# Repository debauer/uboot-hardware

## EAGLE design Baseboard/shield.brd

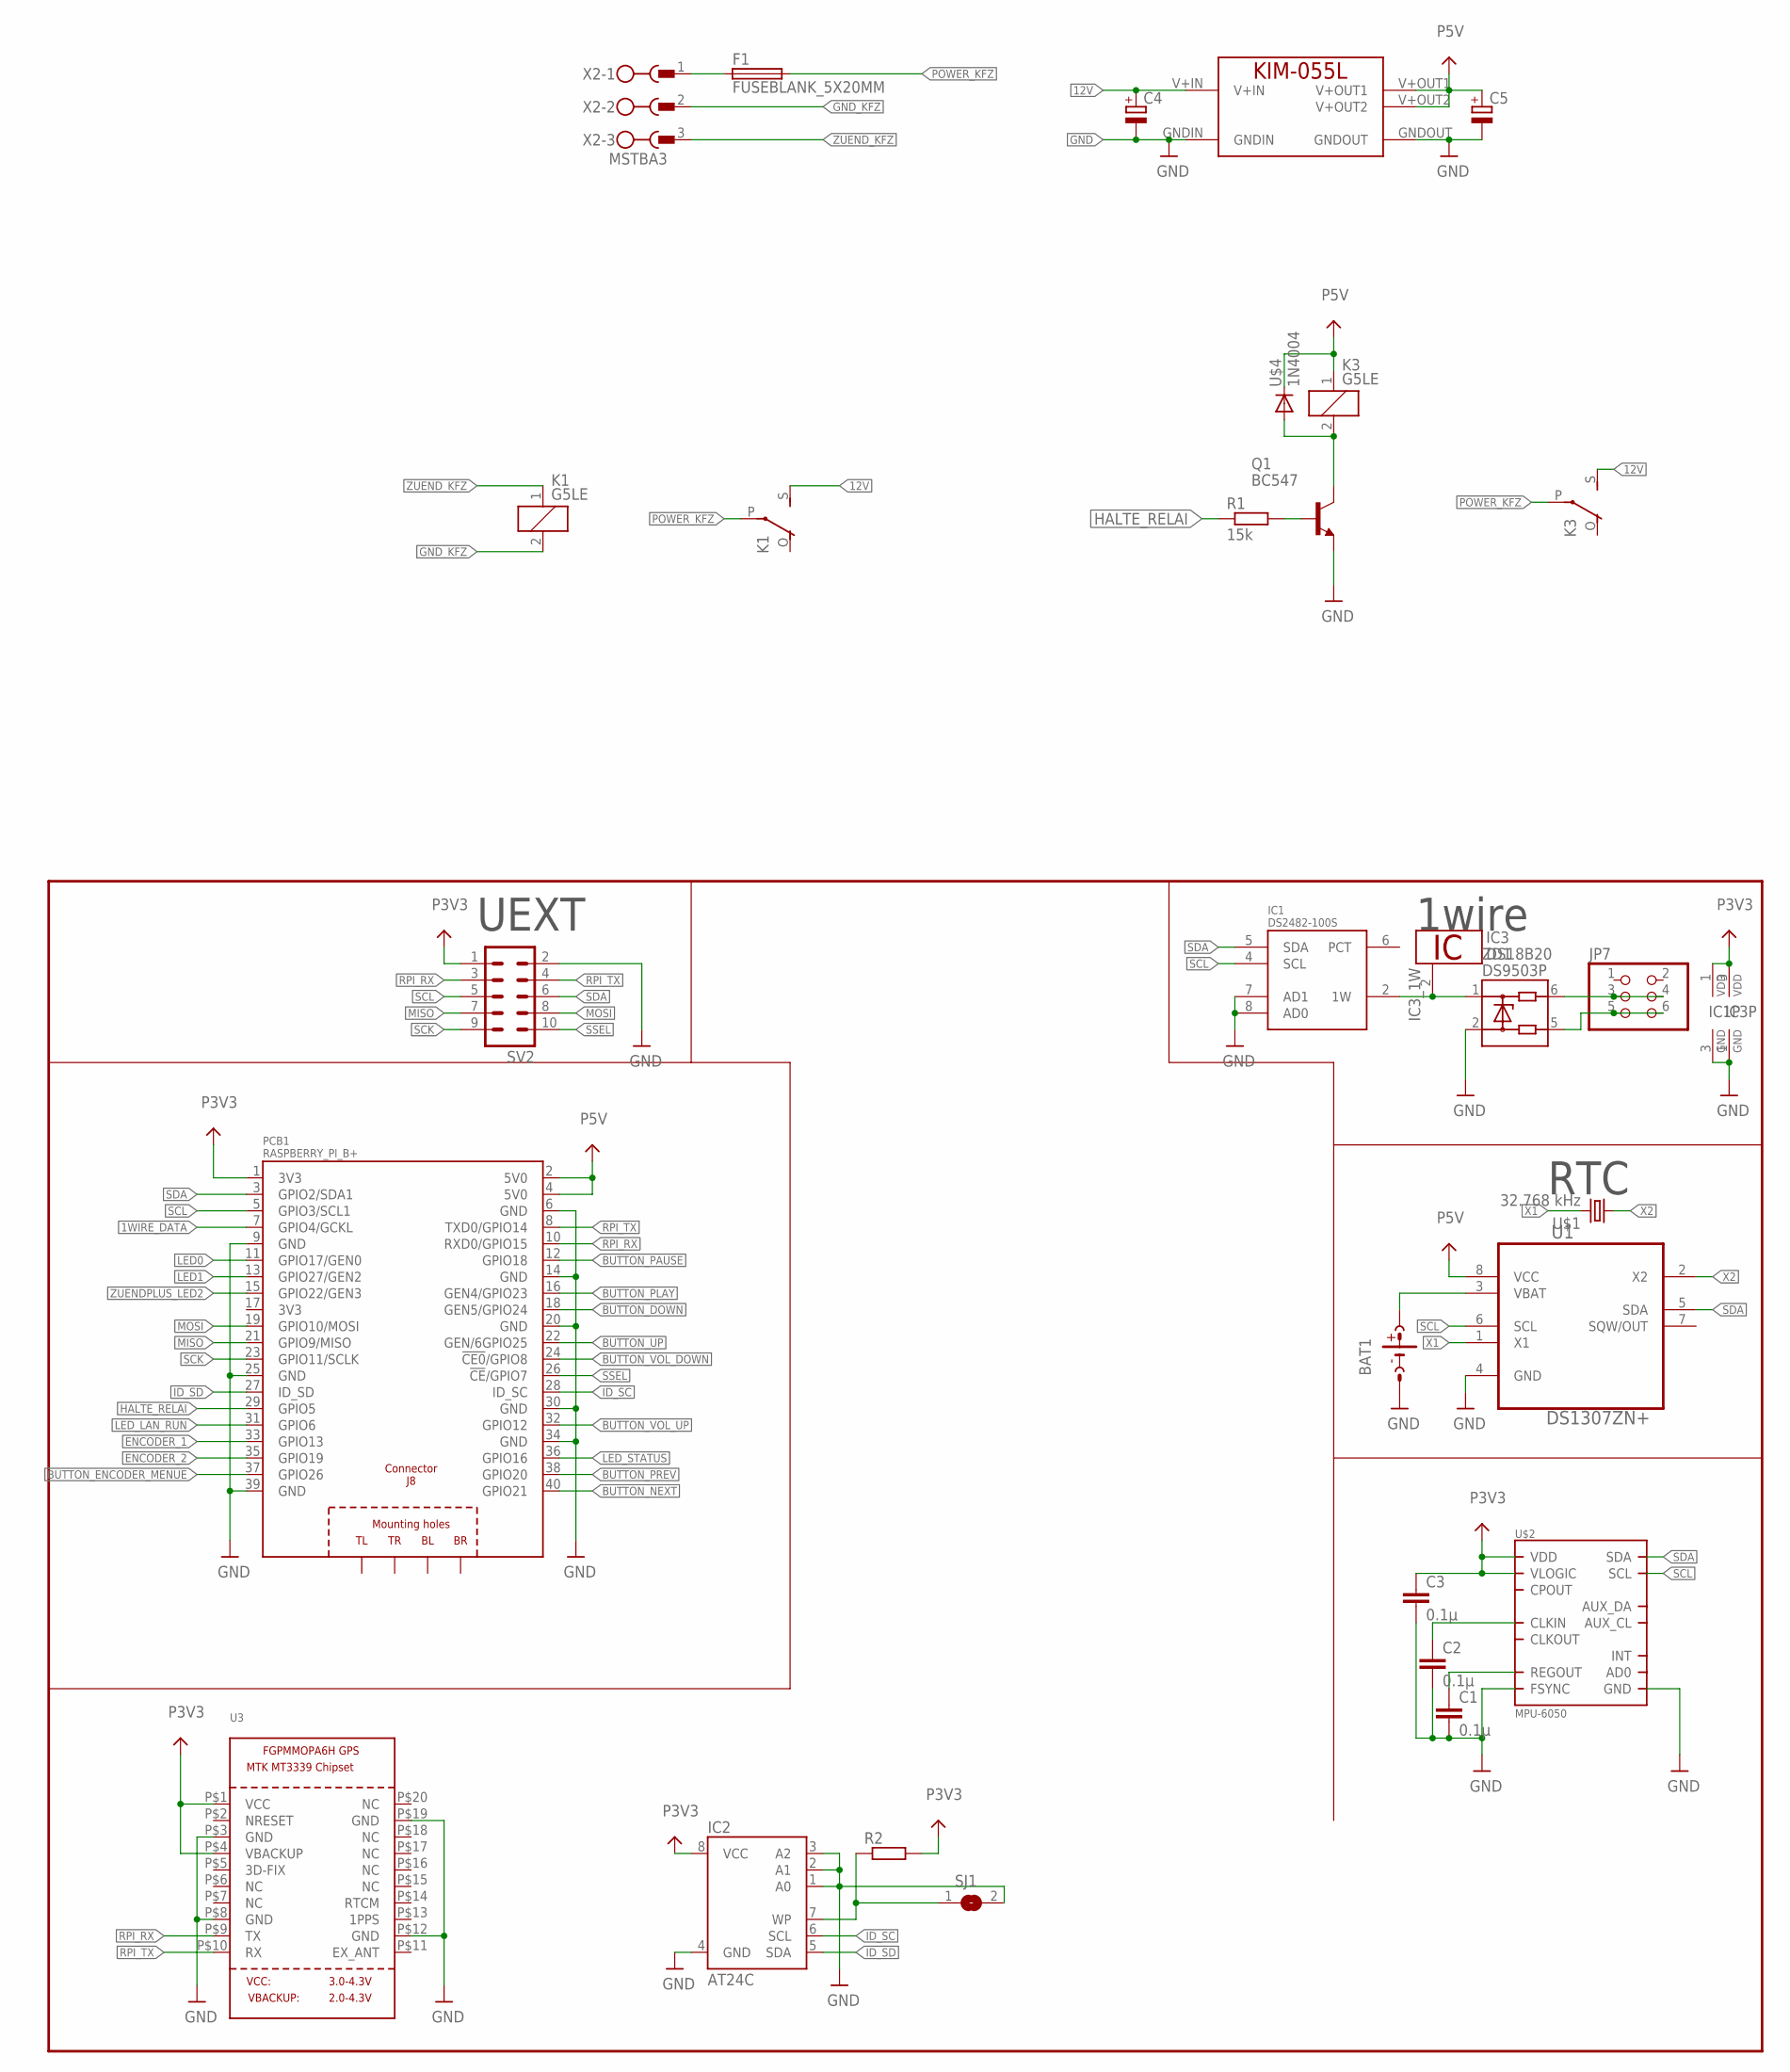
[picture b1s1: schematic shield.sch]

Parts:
BAT1: CR2032; CR2032-SOCKET
C1, C2, C3: 0.1µ; C0805
C4, C5: CPOL-EUE5-13; E5-13
F1: FUSEBLANK_5X20MM; FUSE_HOLDER_5X20MM
IC1: DS2482-100S; SO08
IC2: AT24C; SO08
IC3: DS18B20; TO92-
JP7: PINHD-2X3/90; 2X03/90
K1, K3: G5LE
MOD1: KIM-055L
PCB1: RASPBERRY_PI_B+
Q1: BC547; TO92
R1: 15k; 0207/7
R2: R-EU_R0805; R0805
SJ1: SJM
SV2: ML10
U1: DS1307ZN+; SOIC127P600X175-8N
U3: GPS_FGPMMOPA6H; FGPMMOPA6H
U$1: 32.768 kHz; CC5
U$2: MPU-6050; QFN.24.4X4
U$4: 1N4004; DO41-10
X2: MSTBA3
ZD1: DS9503P; TSOC6

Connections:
1WIRE_DATA: IC1.2 (1W), IC3.2 (1W), PCB1.7 (GPIO4/GCKL), ZD1.1
12V: C4.+, K1.S, K3.S, MOD1.V+IN
BUTTON_DOWN: PCB1.18 (GEN5/GPIO24)
BUTTON_ENCODER_MENUE: PCB1.37 (GPIO26)
BUTTON_NEXT: PCB1.40 (GPIO21)
BUTTON_PAUSE: PCB1.12 (GPIO18)
BUTTON_PLAY: PCB1.16 (GEN4/GPIO23)
BUTTON_PREV: PCB1.38 (GPIO20)
BUTTON_UP: PCB1.22 (GEN/6GPIO25)
BUTTON_VOL_DOWN: PCB1.24 (!CE0!/GPIO8)
BUTTON_VOL_UP: PCB1.32 (GPIO12)
ENCODER_1: PCB1.33 (GPIO13)
ENCODER_2: PCB1.35 (GPIO19)
GND: BAT1.M (NEG), C1.2, C2.2, C3.2, C4.-, C5.-, IC1.3 (GND), IC1.7 (AD1), IC1.8 (AD0), IC2.1 (A0), IC2.2 (A1), IC2.3 (A2), IC2.4 (GND), IC3.1 (GND), MOD1.GNDIN, MOD1.GNDOUT, PCB1.6 (GND), PCB1.14 (GND), PCB1.20 (GND), PCB1.30 (GND), PCB1.34 (GND), Q1.1 (E), SJ1.2, SV2.2, U1.4 (GND), U3.P$3 (GND), U3.P$8 (GND), U3.P$12 (GND), U3.P$19 (GND), U$2.11 (FSYNC), U$2.18 (GND), ZD1.2
GND@1: PCB1.9 (GND), PCB1.25 (GND), PCB1.39 (GND)
GND_KFZ: K1.2, X2.2
HALTE_RELAI: PCB1.29 (GPIO5), R1.1
ID_SC: IC2.6 (SCL), PCB1.28 (ID_SC)
ID_SD: IC2.5 (SDA), PCB1.27 (ID_SD)
LED0: PCB1.11 (GPIO17/GEN0)
LED1: PCB1.13 (GPIO27/GEN2)
LED_LAN_RUN: PCB1.31 (GPIO6)
LED_STATUS: PCB1.36 (GPIO16)
MISO: PCB1.21 (GPIO9/MISO), SV2.7
MOSI: PCB1.19 (GPIO10/MOSI), SV2.8
unnamed: BAT1.P (POS2), U1.3 (VBAT)
unnamed: K3.2, Q1.3 (C), U$4.A
unnamed: C1.1, U$2.10 (REGOUT)
unnamed: C2.1, U$2.1 (CLKIN)
unnamed: IC2.7 (WP), R2.1, SJ1.1
unnamed: Q1.2 (B), R1.2
unnamed: F1.1, X2.1
unnamed: JP7.3, JP7.4, ZD1.6
unnamed: JP7.5, JP7.6, ZD1.5
P3V3: C3.1, IC1.1 (VDD), IC2.8 (VCC), IC3.3 (VDD), PCB1.1 (3V3), R2.2, SV2.1, U3.P$1 (VCC), U3.P$4 (VBACKUP), U$2.8 (VLOGIC), U$2.13 (VDD)
P5V: C5.+, K3.1, MOD1.V+OUT1, MOD1.V+OUT2, PCB1.2 (5V0), PCB1.4 (5V0), U1.8 (VCC), U$4.C
POWER_KFZ: F1.2, K1.P, K3.P
RPI_RX: PCB1.10 (RXD0/GPIO15), SV2.3, U3.P$9 (TX)
RPI_TX: PCB1.8 (TXD0/GPIO14), SV2.4, U3.P$10 (RX)
SCK: PCB1.23 (GPIO11/SCLK), SV2.9
SCL: IC1.4 (SCL), PCB1.5 (GPIO3/SCL1), SV2.5, U1.6 (SCL), U$2.23 (SCL)
SDA: IC1.5 (SDA), PCB1.3 (GPIO2/SDA1), SV2.6, U1.5 (SDA), U$2.24 (SDA)
SSEL: PCB1.26 (!CE!/GPIO7), SV2.10
X1: U1.1 (X1), U$1.P$2 (2)
X2: U1.2 (X2), U$1.P$1 (1)
ZUENDPLUS_LED2: PCB1.15 (GPIO22/GEN3)
ZUEND_KFZ: K1.1, X2.3

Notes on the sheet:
1wire
RTC
UEXT

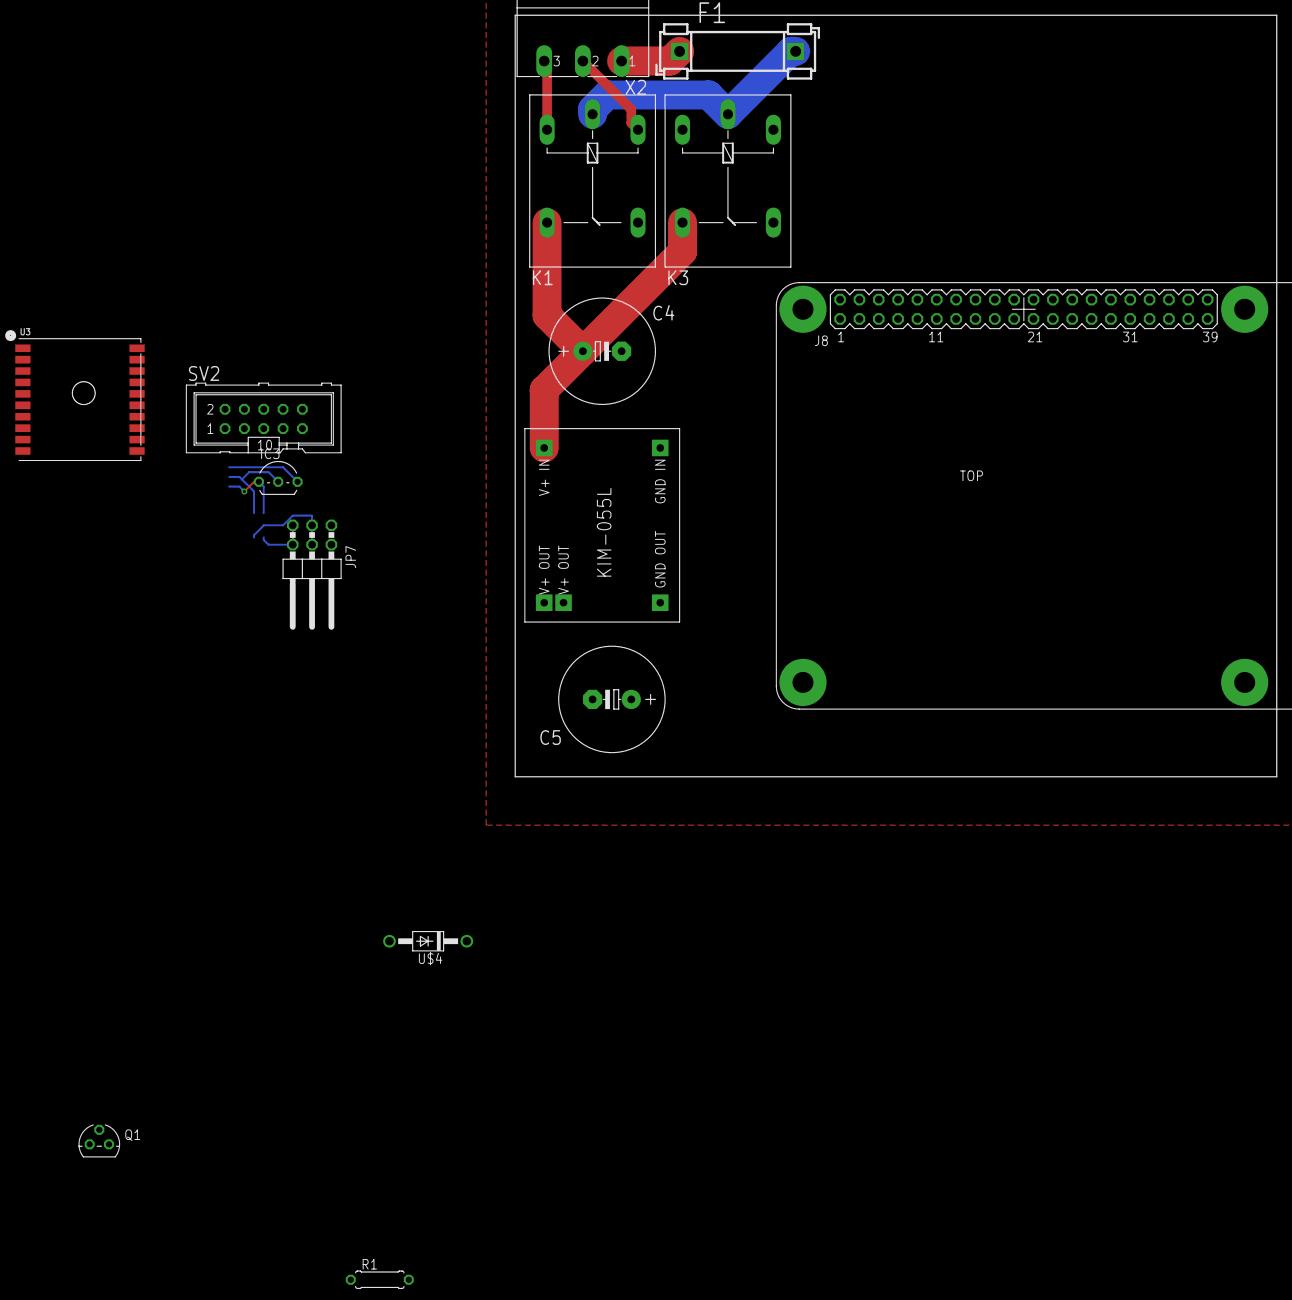
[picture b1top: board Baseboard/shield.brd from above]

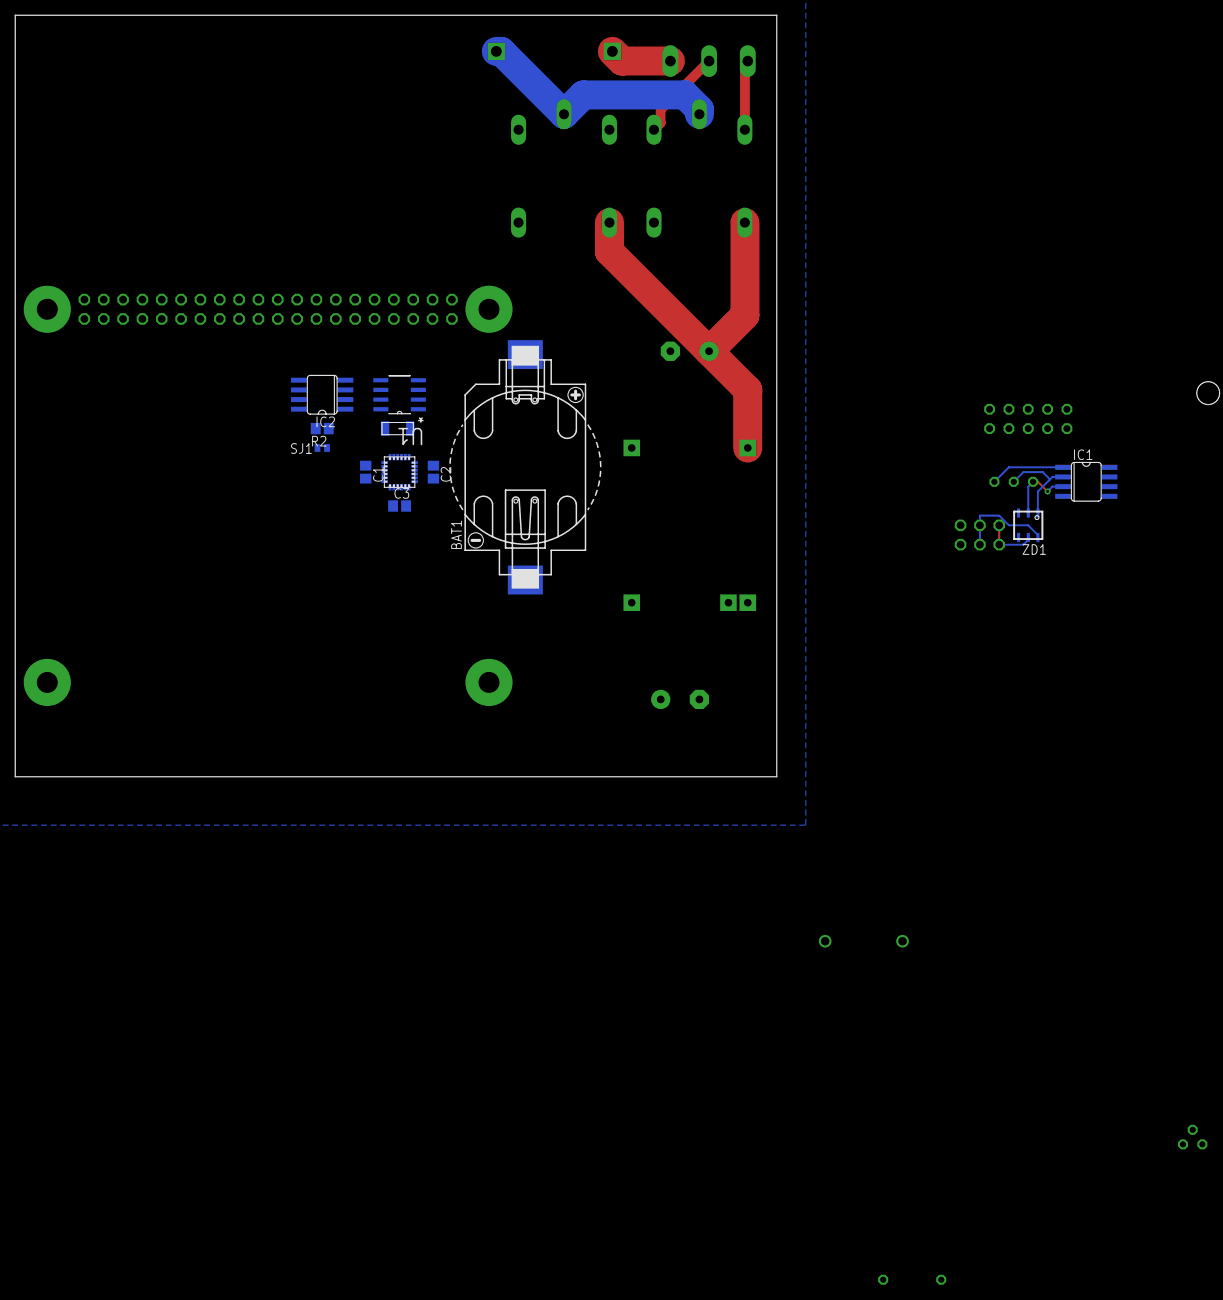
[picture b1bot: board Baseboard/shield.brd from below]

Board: 2 copper layers, 100.0 x 100.0 mm, 27 parts (12 on the bottom side), 31 nets.

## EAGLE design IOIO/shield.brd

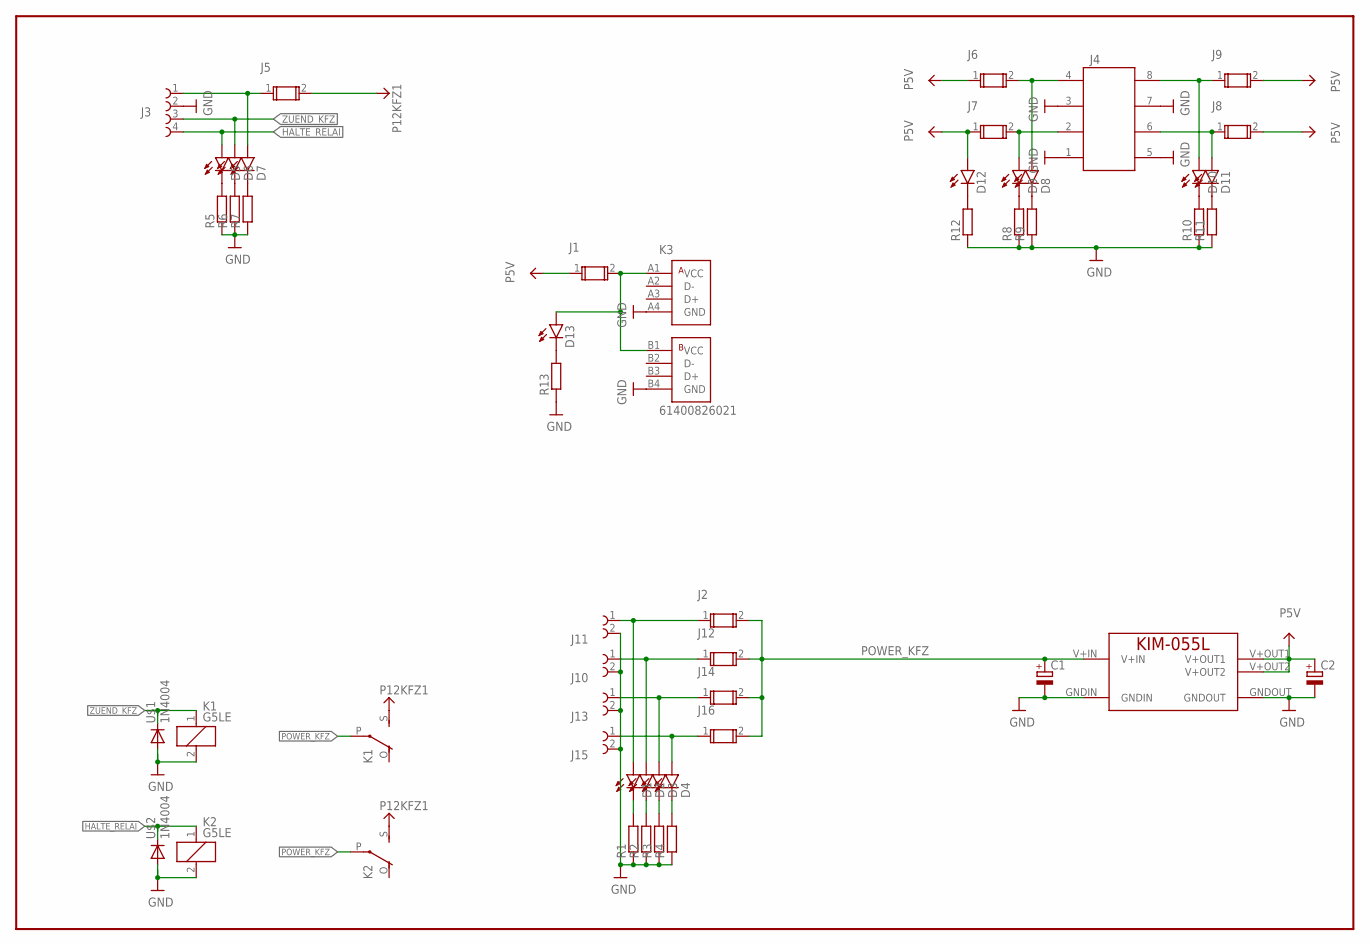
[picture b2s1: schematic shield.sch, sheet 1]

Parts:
C1, C2: CPOL-EUE5-13; E5-13
D1, D2, D3, D4, D5, D6, D7, D8, D9, D10, D11, D12, D13: LED-3MM-NO_SILK; LED3MM-NS
J1, J2, J5, J6, J7, J8, J9, J12, J14, J16: 696101000002
J3: 691325110004
J4: 691327310008
J10, J11, J13, J15: 691322110002
K1, K2: G5LE
K3: 61400826021
MOD1: KIM-055L
R1, R2, R3, R4, R5, R6, R7, R8, R9, R10, R11, R12, R13: R-EU_0309/V; 0309V
U$1, U$2: 1N4004; DO41-10

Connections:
GND: C1.-, C2.-, J3.2 (3), J4.1, J4.3 (5), J4.5 (2), J4.7 (6), J10.2 (1), J11.2 (1), J13.2 (1), J15.2 (1), K1.2, K2.2, K3.A4 (GND), K3.B4 (GND), MOD1.GNDIN, MOD1.GNDOUT, R1.1, R2.1, R3.1, R4.1, R5.1, R6.1, R7.1, R8.1, R9.1, R10.1, R11.1, R12.1, R13.1, U$1.A, U$2.A
HALTE_RELAI: D5.A, J3.4 (1), K2.1, U$2.C
unnamed: D7.A, J3.1 (4), J5.1
unnamed: D11.A, J4.6 (4), J8.1
unnamed: D1.A, J2.1, J11.1 (2)
unnamed: D10.A, J4.8, J9.1
unnamed: D8.A, J4.4 (7), J6.2
unnamed: D9.A, J4.2 (3), J7.2
unnamed: D2.A, J10.1 (2), J12.1
unnamed: D3.A, J13.1 (2), J14.1
unnamed: D4.A, J15.1 (2), J16.1
unnamed: D1.K (C), R1.2
unnamed: D2.K (C), R2.2
unnamed: D3.K (C), R3.2
unnamed: D4.K (C), R4.2
unnamed: D5.K (C), R5.2
unnamed: D6.K (C), R6.2
unnamed: D7.K (C), R7.2
unnamed: D12.K (C), R12.2
unnamed: D9.K (C), R8.2
unnamed: D8.K (C), R9.2
unnamed: D10.K (C), R10.2
unnamed: D11.K (C), R11.2
unnamed: D13.A, J1.2, K3.A1 (VCC), K3.B1 (VCC)
unnamed: D13.K (C), R13.2
P5V: C2.+, D12.A, J1.1, J6.1, J7.1, J8.2, J9.2, MOD1.V+OUT1, MOD1.V+OUT2
P12KFZ1: J5.2, K1.S, K2.S
POWER_KFZ: C1.+, J2.2, J12.2, J14.2, J16.2, K1.P, K2.P, MOD1.V+IN
ZUEND_KFZ: D6.A, J3.3 (2), K1.1, U$1.C

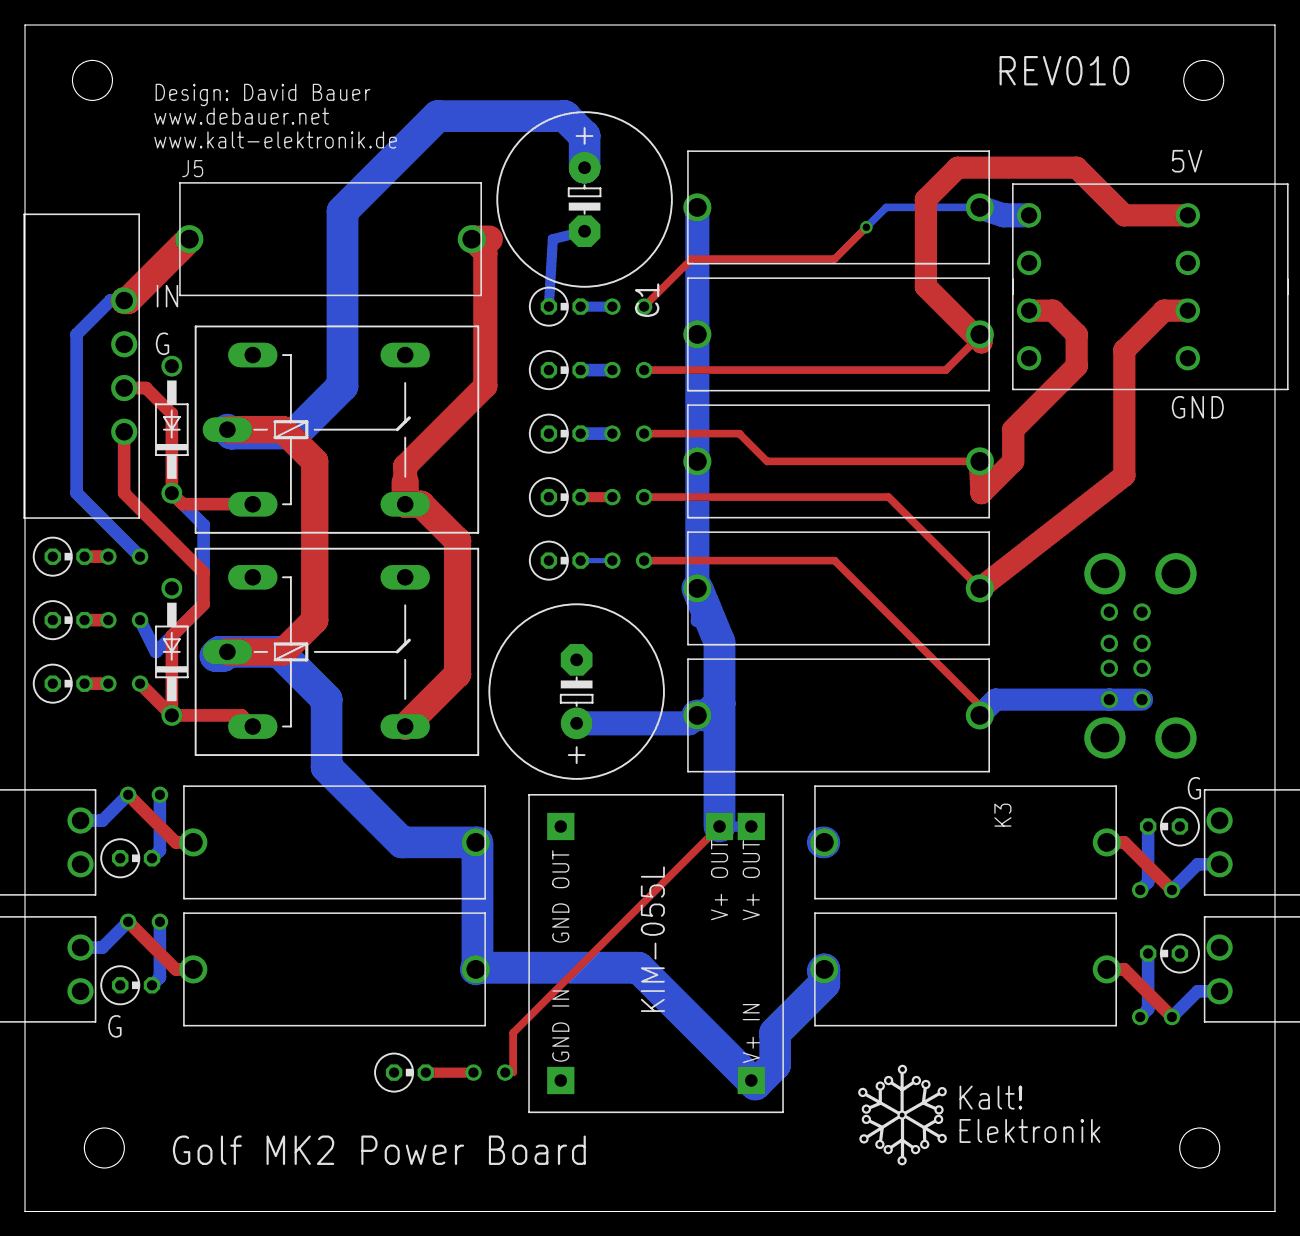
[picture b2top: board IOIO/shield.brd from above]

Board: 2 copper layers, 100.0 x 94.9 mm, 52 parts (0 on the bottom side), 29 nets.

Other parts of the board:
U$11: KALT!ELEKTRONIK
U$12: DISCLAIMER

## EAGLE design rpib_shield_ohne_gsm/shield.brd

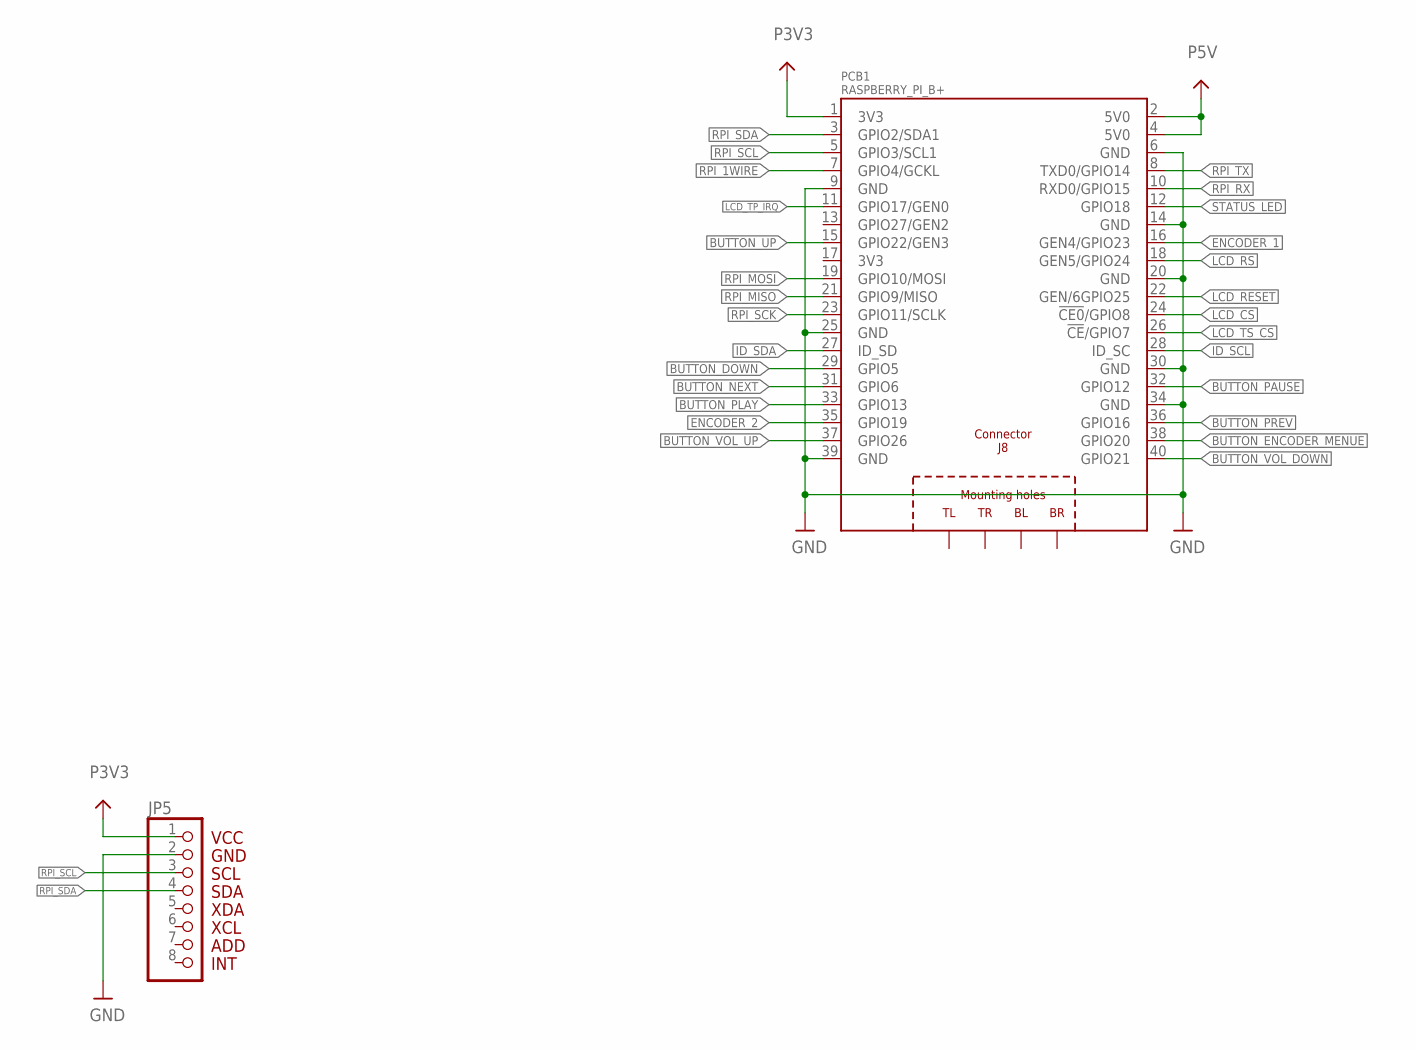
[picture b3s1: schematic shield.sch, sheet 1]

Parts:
JP5: GY-521
PCB1: RASPBERRY_PI_B+

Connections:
BUTTON_DOWN: PCB1.29 (GPIO5); also elsewhere on the board
BUTTON_ENCODER_MENUE: PCB1.38 (GPIO20); also elsewhere on the board
BUTTON_NEXT: PCB1.31 (GPIO6); also elsewhere on the board
BUTTON_PAUSE: PCB1.32 (GPIO12); also elsewhere on the board
BUTTON_PLAY: PCB1.33 (GPIO13); also elsewhere on the board
BUTTON_PREV: PCB1.36 (GPIO16); also elsewhere on the board
BUTTON_UP: PCB1.15 (GPIO22/GEN3); also elsewhere on the board
BUTTON_VOL_DOWN: PCB1.40 (GPIO21); also elsewhere on the board
BUTTON_VOL_UP: PCB1.37 (GPIO26); also elsewhere on the board
ENCODER_1: PCB1.16 (GEN4/GPIO23); also elsewhere on the board
ENCODER_2: PCB1.35 (GPIO19)
GND: JP5.2, PCB1.6 (GND), PCB1.9 (GND), PCB1.14 (GND), PCB1.20 (GND), PCB1.25 (GND), PCB1.30 (GND), PCB1.34 (GND), PCB1.39 (GND); also elsewhere on the board
ID_SCL: PCB1.28 (ID_SC); also elsewhere on the board
ID_SDA: PCB1.27 (ID_SD); also elsewhere on the board
LCD_CS: PCB1.24 (!CE0!/GPIO8)
LCD_RESET: PCB1.22 (GEN/6GPIO25)
LCD_RS: PCB1.18 (GEN5/GPIO24)
LCD_TP_IRQ: PCB1.11 (GPIO17/GEN0)
LCD_TS_CS: PCB1.26 (!CE!/GPIO7); also elsewhere on the board
P3V3: JP5.1, PCB1.1 (3V3); also elsewhere on the board
P5V: PCB1.2 (5V0), PCB1.4 (5V0); also elsewhere on the board
RPI_1WIRE: PCB1.7 (GPIO4/GCKL); also elsewhere on the board
RPI_MISO: PCB1.21 (GPIO9/MISO); also elsewhere on the board
RPI_MOSI: PCB1.19 (GPIO10/MOSI); also elsewhere on the board
RPI_RX: PCB1.10 (RXD0/GPIO15); also elsewhere on the board
RPI_SCK: PCB1.23 (GPIO11/SCLK); also elsewhere on the board
RPI_SCL: JP5.3, PCB1.5 (GPIO3/SCL1); also elsewhere on the board
RPI_SDA: JP5.4, PCB1.3 (GPIO2/SDA1); also elsewhere on the board
RPI_TX: PCB1.8 (TXD0/GPIO14); also elsewhere on the board
STATUS_LED: PCB1.12 (GPIO18); also elsewhere on the board

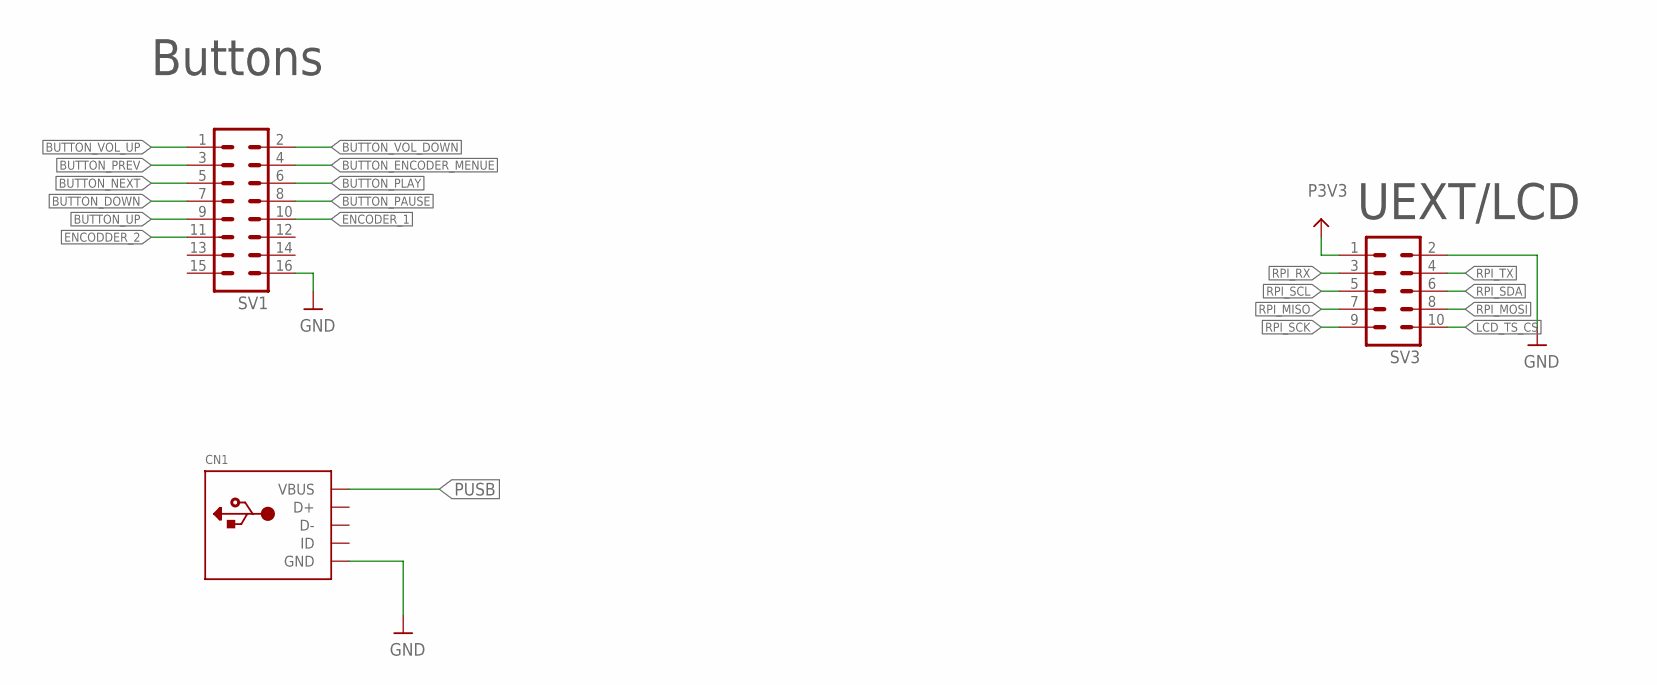
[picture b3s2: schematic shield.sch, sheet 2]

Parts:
CN1: USBMINIB; USB-MINIB
SV1: ML16L
SV3: ML10L

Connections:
BUTTON_DOWN: SV1.7; also elsewhere on the board
BUTTON_ENCODER_MENUE: SV1.4; also elsewhere on the board
BUTTON_NEXT: SV1.5; also elsewhere on the board
BUTTON_PAUSE: SV1.8; also elsewhere on the board
BUTTON_PLAY: SV1.6; also elsewhere on the board
BUTTON_PREV: SV1.3; also elsewhere on the board
BUTTON_UP: SV1.9; also elsewhere on the board
BUTTON_VOL_DOWN: SV1.2; also elsewhere on the board
BUTTON_VOL_UP: SV1.1; also elsewhere on the board
ENCODDER_2: SV1.11
ENCODER_1: SV1.10; also elsewhere on the board
GND: CN1.GND, SV1.16, SV3.2; also elsewhere on the board
LCD_TS_CS: SV3.10; also elsewhere on the board
P3V3: SV3.1; also elsewhere on the board
PUSB: CN1.VBUS; also elsewhere on the board
RPI_MISO: SV3.7; also elsewhere on the board
RPI_MOSI: SV3.8; also elsewhere on the board
RPI_RX: SV3.3; also elsewhere on the board
RPI_SCK: SV3.9; also elsewhere on the board
RPI_SCL: SV3.5; also elsewhere on the board
RPI_SDA: SV3.6; also elsewhere on the board
RPI_TX: SV3.4; also elsewhere on the board

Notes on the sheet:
UEXT/LCD
Buttons

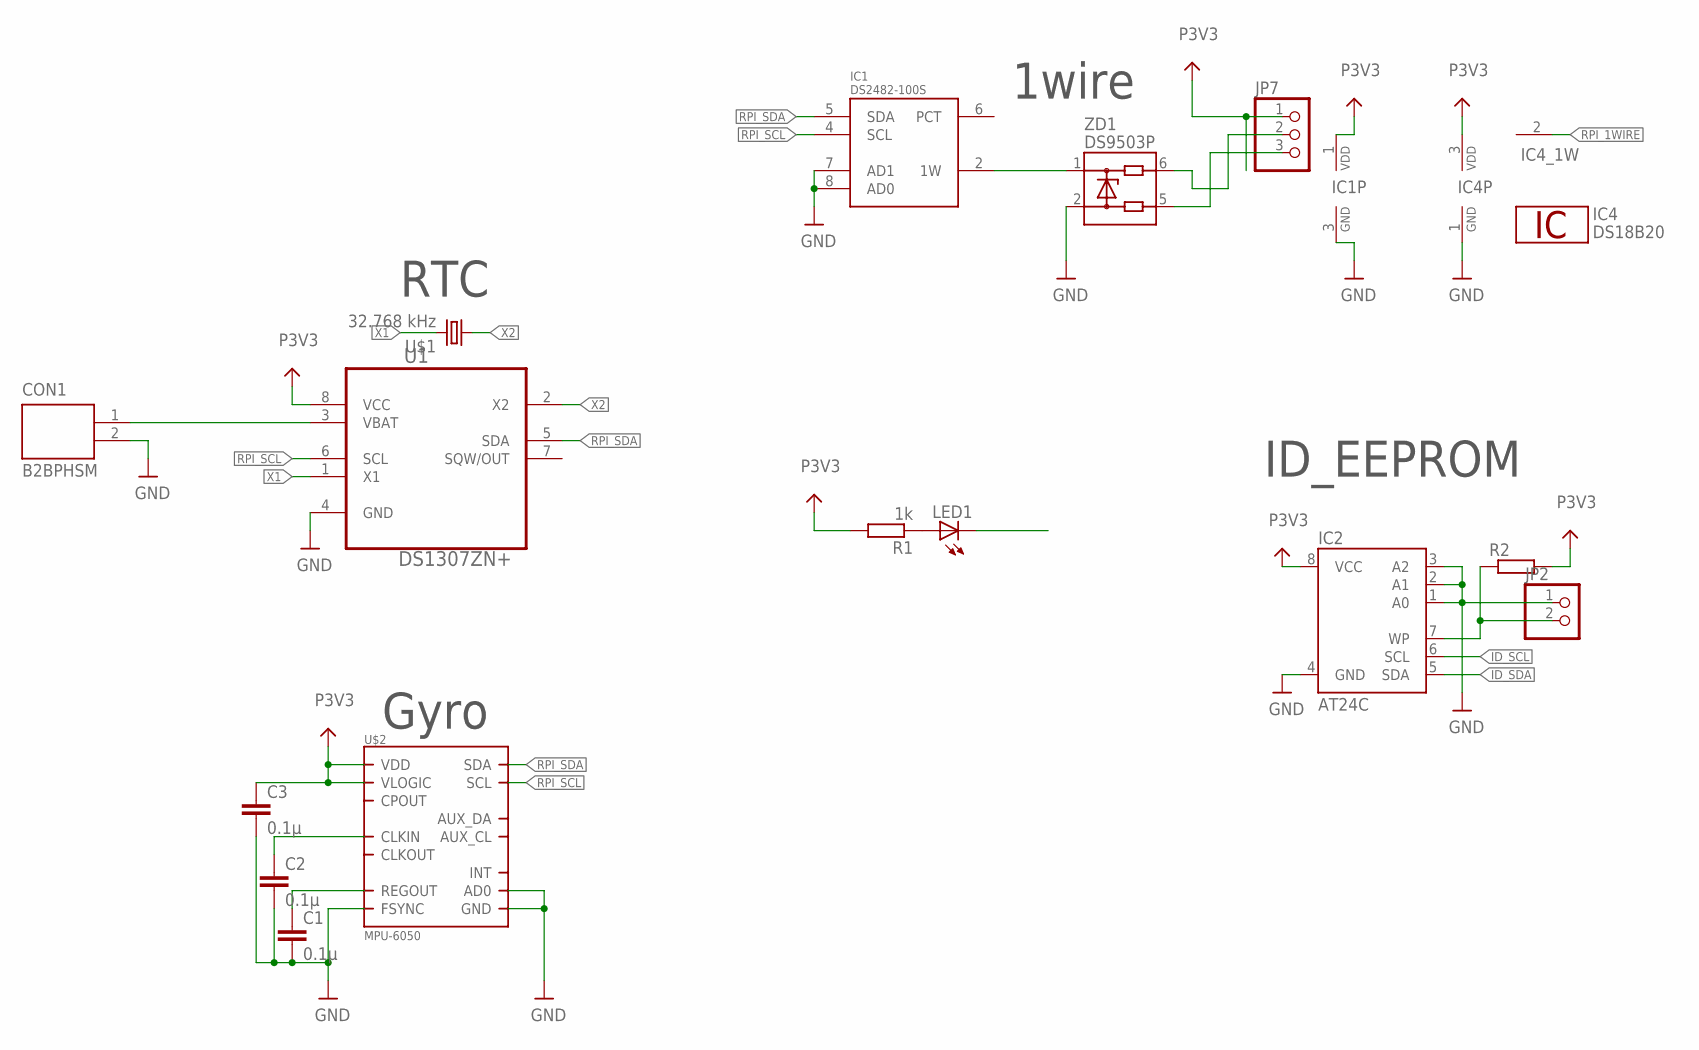
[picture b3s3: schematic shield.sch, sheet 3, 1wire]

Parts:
C1, C2, C3: 0.1µ; C0805
CON1: B2BPHSM
IC1: DS2482-100S; SO08
IC2: AT24C; SO08
IC4: DS18B20; TO92-
JP2: PINHD-1X2; 1X02
JP7: PINHD-1X3; 1X03
LED1: LEDCHIP-LED0805; CHIP-LED0805
R1: 1k; R1206
R2: R-EU_R0805; R0805
U1: DS1307ZN+; SOIC127P600X175-8N
U$1: 32.768 kHz; CC5
U$2: MPU-6050; QFN.24.4X4
ZD1: DS9503P; TSOC6

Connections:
GND: C1.2, C2.2, C3.2, CON1.2, IC1.3 (GND), IC1.7 (AD1), IC1.8 (AD0), IC2.1 (A0), IC2.2 (A1), IC2.3 (A2), IC2.4 (GND), IC4.1 (GND), JP2.1, U1.4 (GND), U$2.9 (AD0), U$2.11 (FSYNC), U$2.18 (GND), ZD1.2; also elsewhere on the board
ID_SCL: IC2.6 (SCL); also elsewhere on the board
ID_SDA: IC2.5 (SDA); also elsewhere on the board
unnamed: CON1.1, U1.3 (VBAT)
unnamed: JP7.3, ZD1.5
unnamed: C1.1, U$2.10 (REGOUT)
unnamed: C2.1, U$2.1 (CLKIN)
unnamed: IC2.7 (WP), JP2.2, R2.1
unnamed: JP7.2, ZD1.6
unnamed: LED1.A, R1.1
unnamed: IC1.2 (1W), ZD1.1
P3V3: C3.1, IC1.1 (VDD), IC2.8 (VCC), IC4.3 (VDD), JP7.1, R1.2, R2.2, U1.8 (VCC), U$2.8 (VLOGIC), U$2.13 (VDD); also elsewhere on the board
RPI_1WIRE: IC4.2 (1W); also elsewhere on the board
RPI_SCL: IC1.4 (SCL), U1.6 (SCL), U$2.23 (SCL); also elsewhere on the board
RPI_SDA: IC1.5 (SDA), U1.5 (SDA), U$2.24 (SDA); also elsewhere on the board
STATUS_LED: LED1.C; also elsewhere on the board
X1: U1.1 (X1), U$1.P$2 (2)
X2: U1.2 (X2), U$1.P$1 (1)

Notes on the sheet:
1wire
RTC
Gyro
ID_EEPROM

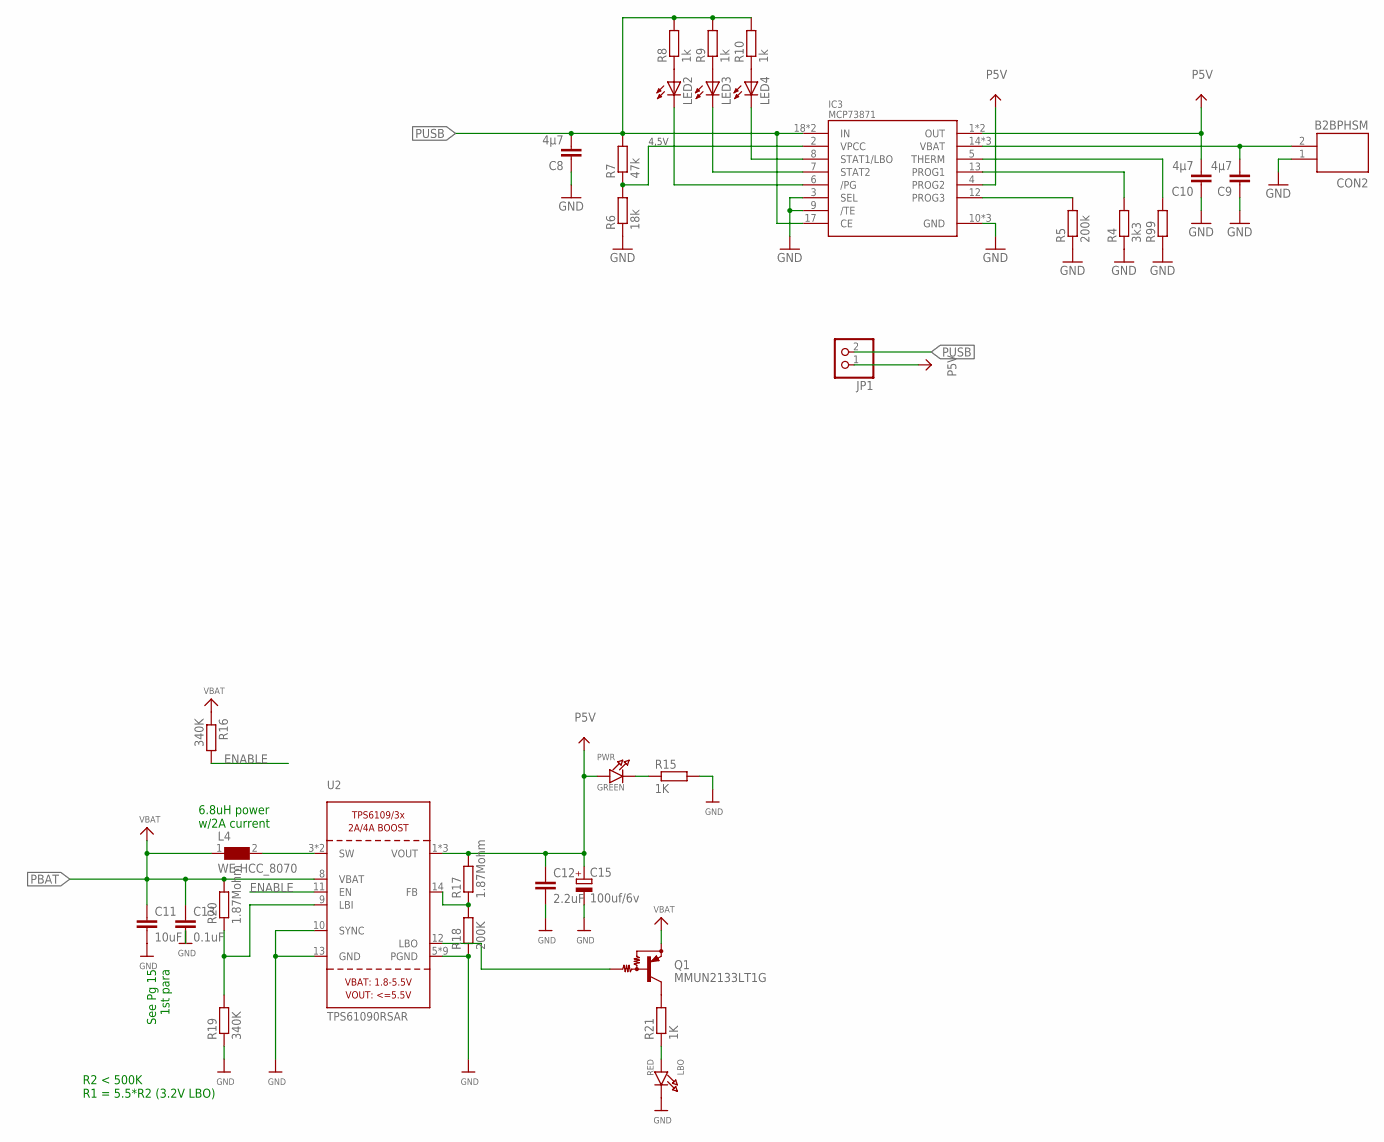
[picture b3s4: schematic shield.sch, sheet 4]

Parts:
C8, C9, C10: 4µ7; C1206
C11: 10uF; C1206
C12: 2.2uF; C1206
C13: 0.1uF; C1206
C15: 100uf/6v; B/3528-21W
CON2: B2BPHSM
IC3: MCP73871; LQFN-20
JP1: PINHD-1X2; 1X02
L4: WE-HCC_8070
LBO: RED; CHIPLED_0805_NOOUTLINE
LED2, LED3, LED4: LEDCHIP-LED0805; CHIP-LED0805
PWR: GREEN; CHIPLED_0805_NOOUTLINE
Q1: MMUN2133LT1G; SC59-BEC
R4: 3k3; R1206
R5: 200k; R1206
R6: 18k; R1206
R7: 47k; R1206
R8, R9, R10: 1k; R1206
R15, R21: 1K; R1206
R16, R19: 340K; R1206
R17, R20: 1.87Mohm; R1206
R18: 200K; R1206
R99: R-EU_R1206; R1206
U2: TPS61090RSAR; PVQFN-16

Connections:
ENABLE: R16.2, U2.11 (EN)
GND: C8.1, C9.1, C10.1, C11.2, C12.2, C13.2, C15.-, CON2.1, IC3.3 (SEL), IC3.9 (/TE), IC3.10 (GND), IC3.11 (GND), IC3.EP (GND), LBO.C, R4.1, R5.1, R6.1, R15.2, R18.1, R19.1, R99.1, U2.5 (PGND), U2.6 (PGND), U2.7 (PGND), U2.10 (SYNC), U2.13 (GND), U2.P$18 (PGND), U2.P$19 (PGND), U2.P$20 (PGND), U2.P$21 (PGND), U2.P$22 (PGND), U2.THERMAL (PGND); also elsewhere on the board
LBO: Q1.B, U2.12 (LBO)
unnamed: L4.2, U2.3 (SW), U2.4 (SW)
unnamed: IC3.5 (THERM), R99.2
unnamed: IC3.13 (PROG1), R4.2
unnamed: IC3.12 (PROG3), R5.2
unnamed: IC3.2 (VPCC), R6.2, R7.1
unnamed: LED2.A, R8.1
unnamed: LED3.A, R9.1
unnamed: LED4.A, R10.1
unnamed: IC3.8 (STAT1/LBO), LED4.C
unnamed: IC3.7 (STAT2), LED3.C
unnamed: IC3.6 (/PG), LED2.C
unnamed: R19.2, R20.1, U2.9 (LBI)
unnamed: PWR.C, R15.1
unnamed: R17.1, R18.2, U2.14 (FB)
unnamed: LBO.A, R21.1
unnamed: Q1.C, R21.2
P5V: C10.2, C12.1, C15.+, IC3.1 (OUT), IC3.4 (PROG2), IC3.20 (OUT), JP1.1, PWR.A, R17.2, U2.1 (VOUT), U2.15 (VOUT), U2.16 (VOUT); also elsewhere on the board
PBAT: C9.2, C11.1, C13.1, CON2.2, IC3.14 (VBAT), IC3.15 (VBAT), IC3.16 (VBAT), L4.1, R20.2, U2.8 (VBAT)
PUSB: C8.2, IC3.17 (CE), IC3.18 (IN), IC3.19 (IN), JP1.2, R7.2, R8.2, R9.2, R10.2; also elsewhere on the board
VBAT: Q1.E, R16.1

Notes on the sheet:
4,5V
See Pg 15 1st para
6.8uH power w/2A current
R2 < 500K R1 = 5.5*R2 (3.2V LBO)

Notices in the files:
parts and their libraries:
Wuerth_TERMINAL_BLOCKS-rev16e: Copyright: Würth Elektronik
microbuilder: This work is placed in the public domain, and may be freely used for commercial and non-commercial work with the following conditions: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
